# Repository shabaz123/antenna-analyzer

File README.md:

# Antenna Analyzer
This repository contains the detail to construct a VHF/UHF antenna analyzer instrument designed by VK5JST (Amateur Radio, May 2005). Refer to the original article for more information concerning it. The design was entered into KiCad software by TDARS, to create the printed circuit boards described here.

# Overview
The analyzer has two connections; one from the radio transmitter (2W max, but you could use an attenuator), and one to the antenna. Note that the instrument also supports HF, but you'll still need to limit power to 2W max, or use an attenuator.

There's a 4-position rotary selector knob. By using that, it is possible to select SWR or R/Z modes, and observe these values on the built-in moving-coil meter movement. The meter is fitted with a detailed scale, although the diagram here just shown LO/HI.

# Circuit Diagram

# One-Time Calibration
To calibrate the instrument one-time after building it, you just need a HF signal source of adjustable power. Do the following:

(1) Connect a low-power HF source to the RF input on the instrument, and ensure that nothing is attached to the antenna connector (to simulate a bad antenna)

(2) Set the selector knob to the leftmost position which is the **Check Input** position.

(3) Slowly ramp up the input power until the meter scale reaches the center of the '**INPUT OK**' section, which may occur at about 1W of transmitted power

(4) Set the selector knob to next position (**Set FSD**), and then adjust the **front panel potentiometer** until the needle reaches the full scale position

(5) Set the selector knob to the next position (**SWR**), and adjust the trimmer resistor labeled **TP1** to place the needle at the full scale position again

(6) Set the selector knob to the last remaining position (**R/Z**) and adjust the trimmer resistor labeled **TP2** to place the needle again at the full scale position

(7) All is done!

# Using It

In normal use, connect the instrument up to your transmitter (maximum 2W! or use an attenuator) as well as your antenna. Then, follow these steps:

(1) Turn the selector knob to the Set FSD position, and then, at your desired transmit frequency, transmit at approximately half a Watt, or 1W (2W max! or use an attenuator). Turn the rotary potentiometer on the front panel until the meter needle is at max.

(2) Now you are free to select either the SWR or R/Z positions, and examine the values. A good SWR value will be low (leftmost on the meter dial), and a good impedance value will be 50 ohms (close to the center of the meter dial).

(3) By slowly varying the transmit frequency, you should be able to find the antenna resonant frequency, by looking at the impedance. Picture a valley. If you traverse from low to high frequency, then the impedance will reduce down toward 50 ohm, and then beyond a certain frequency it will start increasing. The impedance valley bottom location is where the antenna is resonant.

# Main Circuit Board (with snap-off areas)
The instrument is built using a printed circuit board that has snap-away sections for the rotary controls. Most of the parts are large surface-mount, which is easy to assemble using a good pair of tweezers and a decent soldering iron. Note: Don't solder the BNC and N sockets, until you've looked at the section further below titled 'End Panel'.

This is what the underside looks like:

As you can see, there are snap-off areas for the controls. Note that the PCB manufacturer may ask for an additional charge subsequently as a result of that. For instance, see JLC PCB rules here: https://jlcpcb.com/help/article/in-what-cases-will-there-be-charged-extra

# Alternative Main Circuit Board (with no snap-off areas)
If desired, you could order a PCB without the snap-off areas. You'd need to manually wire the controls (rotary switch and potentiometer) and resistor R8, or use a Flex PCB which is described further below. 

# Wire Link! And Flex Connector Orientation

Important - don't forget to solder the wire link on the main board! It should be soldered on the underside as shown in the photo (so that the PCB ground plane can shield it from the component side).

Also, note how the flex connector is oriented in the photo below. This orientation will hopefully allow it to make good contact with the copper side of the flex PCB.

# Enclosure Planning
You could 3D-print an enclosure if desired. There are two existing 3D printed enclosure styles, developed by Paul M0PLA.

The difference is that style V3 has a sloped top. To print either of them, download the [style V1 STL file](https://github.com/shabaz123/antenna-analyzer/raw/refs/heads/main/3d-renders/swr-box-v1.stl) or the [style V3 STL file](https://github.com/shabaz123/antenna-analyzer/raw/refs/heads/main/3d-renders/swr-box-v3.stl) and 3D-print it (or use a 3D print service).

A wood enclosure is another possibility.
For the full set of dimensions, refer to the "Dimensions" section further below.

Use the front panel PCB, and the end panel PCB, as guides to create the enclosure, and confirm they will fit.

# Flex PCB Controls
If you like, you could use a flexible PCB for the controls and resistor R8. This is what the design looks like:

Here is the 3D view of it:

Here is the underside view of it:

The potentiometer and rotary switch bodies both have a little protrusion key that is used to prevent them rotating along with the shaft. The top panel PCB does not have keyholes for that, so you'll need to dremel or file off the protrusions or find some other way of removing them. I used heavy-duty wire cutters, but it will probably damage the cutters slightly. 
You could use epoxy glue to secure the potentiometer bodies as shown in the photos below. I decided not to use the shaft nuts to secure the potentiometer and rotary switch, because I wanted to recess them a little bit, and I just used glue. Perhaps a 3D-printed mount could be glued onto the underside of the top panel, to make them flush from the top side.

Here is what it looks like when the flex PCB is assembled:

To use this flex PCB, you'll need to attach a Flat Flexible Cable (FFC) connector onto the mainboard:

The connector is available from AliExpess, search for **FPC 2.54mm Pitch Connector Flat Flexible Cable** and select an 8-way connector. There are straight and right-angle options. The 3D render above shows a right-angle connector, but a straight connector is probably easier to install without hitting the meter. 

## Important: Connector Orientation
Install the connector such that the Pin 1 marking on the flexible PCB mates with Pin 1 on the mainboard, which is indicated by a square pad. 

NOTE: You also have to ensure that the springy side of the terminal inside the connector mates with the copper side of the flexible PCB, to make good contact. If you're unsure, use a multimeter set to continuity mode and check there is good contact before soldering the connector. This will help eliminate the risk of installing the connector the wrong way around.

# End Panel
If you don't have the ability to drill holes, then optionally, an end panel printed circuit board can be created too. This eliminates needing to drill any holes.

The BNC and N sockets are simply screwed onto the panel (order is: put crinkle washer on first, then the ring tag, then the nut), and the ring tags can be soldered down (it will be easier if you slightly bend the ring tag terminal beforehand).

After you've done that, the BNC and N connectors can be soldered to the main board PCB and then solder the edge of the main board against the horizontal bare copper area on the end panel. 

NOTE: It's probably a good idea to use epoxy glue to secure the RF connectors to their nuts, and to the PCB, so that the RF connectors cannot rotate even slightly (which would tear the RF connector center pin connection to the PCB tracks!

# Meter Dial
To remove the existing meter dial (100uA scale) remove the meter side ears (they look like paddles, they might not be fitted to the meter as supplied). Next, carefully remove the black bezel from the meter. It just unclips, if you gently bend the side lobes of the bezel just a fraction of a degree (careful, they can break!).

There is a white wedge-shaped meter zero position adjustment on the front of the meter. Rotate it so that the white wedge is centered for now. Next, unscrew the two small screws that hold the front clear plastic to the meter, and carefully lift off the front plastic. This is easier when that white wedge has been centered. 

You'll see that the meter dial/scale is a thin aluminium plate that has been painted white with black lettering. Unscrew the two screws that hold the meter dial to the meter, and then slide it out, without accidentally bending the meter needle!

There are two options as to how to replace the meter dial.

(1) Print off the [SVG meter dial](https://github.com/shabaz123/antenna-analyzer/raw/refs/heads/main/images/meter-dial-antenna-analyzer.svg) onto a sheet of paper (you may have to experiment with it to size it perfectly) and then cut and glue it to the plain aluminium side of the existing meter dial. An excellent thin watery glue is "Tombow Mono Multi Liquid Glue" intended for cardboard.

(2) Use the [meter dial Gerber file](https://github.com/shabaz123/antenna-analyzer/raw/refs/heads/main/gerbers/meter-dial-antenna-analyzer-gerbers.zip) and upload it to a PCB manufacturer website, selecting 0.8 mm thickness aluminium PCB. When it arrives, it should be a direct replacement for the existing meter dial, although it will be slightly thicker (ideally it would be 0.25 - 0.3 mm thick, but that's not feasible at a reasonable cost from PCB manufacturers).

# Top Panel
Optionally, if desired, you could use the top panel printed circuit board, if you don't have a way to cut out a meter panel rectangular hole. The top panel eliminates needing to cut out anything!

The meter side ears are removed, then carefully unclip the black bezel and then insert the bezel into the top panel, and then the meter is fitted to the bezel from below the top panel, and then the side ears are fitted on, and rotated until the meter is held in position firmly.

# Final Assembly

The top panel is screwed into the enclosure first. Then, the end panel (with the main board soldered on) is brought into position, to plug in the flex PCB. 

The photo here shows the flex PCB plugged into the main board:

Screw the end panel into position.

All is complete, ready for testing and calibration!

# Dimensions
The information in these photos/diagrams may be helpful if you're designing an enclosure.

# Ordering the Circuit Boards

You'll need the following zip files:

[main-board-gerbers.zip](https://github.com/shabaz123/antenna-analyzer/raw/refs/heads/main/gerbers/main-board-gerbers.zip)

[end-panel-gerbers.zip](https://github.com/shabaz123/antenna-analyzer/raw/refs/heads/main/gerbers/end-panel-gerbers.zip)

[top-panel-gerbers.zip](https://github.com/shabaz123/antenna-analyzer/raw/refs/heads/main/gerbers/top-panel-gerbers.zip)

[meter-dial-antenna-analyzer-gerbers.zip](https://github.com/shabaz123/antenna-analyzer/raw/refs/heads/main/gerbers/meter-dial-antenna-analyzer-gerbers.zip)

If you intend to go the flexible controls PCB route, then you don't need the main-board-gerbers.zip file, and instead, you need to replace that with these two files:

[mainboard-only-no-snap-off-areas.zip](https://github.com/shabaz123/antenna-analyzer/raw/refs/heads/main/gerbers/mainboard-only-no-snap-off-areas.zip)

[controls-flex-gerbers.zip](https://github.com/shabaz123/antenna-analyzer/raw/refs/heads/main/gerbers/controls-flex-gerbers.zip)

To order, go to any PCB manufacturer, e.g. JLCPCB, register for an account, then click on **Order Now** and then click on **Add Gerber File**. 

Select one of the zip files and upload it. You can accept all the defaults, but feel free to play around with the PCB color options (some may cost more, or take a couple of days longer to manufacture). Optionally, select **Remove Mark** which is in the **Mark on PCB** section (if you don't select Remove Mark, then a little serial number will appear on your board, and you might not want that for cosmetic reasons). Once you're done, click the **Save to Cart** button. 

Repeat for the other zip files as required. For the meter dial, make sure you select 0.8 mm thickness, rather than the default 1.6 mm thickness. When you checkout the order, you'll see a list of all of the boards that you uploaded. Click on the checkbox on the left side, to select all the items. 

Note: If you're ordering the flexible controls PCB, then you need to perform the following steps:

Select **Global Shipping Direct Line**, which is usually the far cheaper delivery option. You can confirm the price in the box on the right, prior to finally paying (with, say PayPal).

Note that if you're ordering the flexible PCB, then it's highly recommended to select the 'Payment after Review' option, so that the manufacturer can e-mail you any queries that they may have. If they have trouble understanding what the flexible PCB is supposed to look like, you could send them the flex PCB layout and 3D render screenshots, so that they have some context.

# Parts List

The PDF parts list is downloadable here: 

[parts-list.pdf](https://github.com/shabaz123/antenna-analyzer/raw/refs/heads/main/components/parts-list.pdf)

**NOTE**: The PDF parts list is missing the Flat Flex Cable (FFC) connector, which is optional, it is only required if you're using the flex PCB.

The contents are reproduced here for convenience (including the FFC connector):

**Row**|**Identifier**|**Value**|**Qty**|**Description**|**Source**|**Part Code**|**Approx Total GBP**
:-----:|:-----:|:-----:|:-----:|:-----:|:-----:|:-----:|:-----:
1|R1,R2,R3|3 x 150R Parallel|9|1206 150 ohm Resistor Thick Film 0.75W|Mouser|SG73P2BTTD151G|0.55
2|R4|15k|1|0805 Resistor|Mouser|RCG080515K0FKEA|0.12
3|R5|10k|1|0805 Resistor|Mouser|RCG080510K0FKEA|0.12
4|R6|27k|1|0805 Resistor|Mouser|RCS080527K0FKEA|0.27
5|R7|56k|1|0805 Resistor|Mouser|RCS080556K0FKEA|0.11
6|R8|470R|1|0805 Resistor|Mouser|CRCW0805470RFKEA|0.07
7|C1,C2,C3|470p|3|0805 Capacitor NP0 470pF|Mouser|08055A471J4T2A|0.54
8|C4,C5,C6|100n|3|0805 Capacitor X7R 100nF|Mouser|KAM21BR71H104JT|0.21
9|D1,D2,D3|1N5711W-7-F|3|Schottky Diode SOD-123|Mouser|1N5711W-7-F|0.35
10|TP1,TP2|10k Trimmer|2|Trimmer Resistor 10k 3386P|Mouser|3386P-1-103T|3.68
11|SK3|BNC Socket|1|BNC Socket 031-221-RFX|Mouser|031-221-RFX|2.49
12|SK4|N Socket|1|N Socket 1-1337417-0|Mouser|1-1337417-0|6.18
13|M1|100uA Panel Meter|1|85C17 100uA Panel Meter|AliExpress|85C17 100uA|3.41
14|P1|5k LIN (B) Potentiometer|1|RV097 Linear (B) 5k Potentiometer |AliExpress|RV097 B 5k|0.41
15|SW1|RS1010 Rotary Switch|1|RS1010 2 Pole 4 Way Switch|AliExpress|RS1010 2 Pole 4|0.88
16|n/a|Knob|2|Potentiometer Knob 10mm dia|AliExpress|Knob Flower Axis Diameter 10mm|0.38
17|n/a|8-way Cable|1|2.54 mm Pitch Grey Flat Cable 70mm|AliExpress|2.54mm Flat Cable 8P 70mm|0.29
18|n/a|4-way Cable|1|2.54 mm Pitch Grey Flat Cable 70mm|AliExpress|2.54mm Flat Cable 4P 70mm|0.28
19|n/a|FFC Connector|1|FPC 2.54mm Pitch Connector Flat Flexible Cable 8-way Straight (ideally)|AliExpress|FPC 2.54mm Pitch Connector Flat Flexible Cable Straight|0.17

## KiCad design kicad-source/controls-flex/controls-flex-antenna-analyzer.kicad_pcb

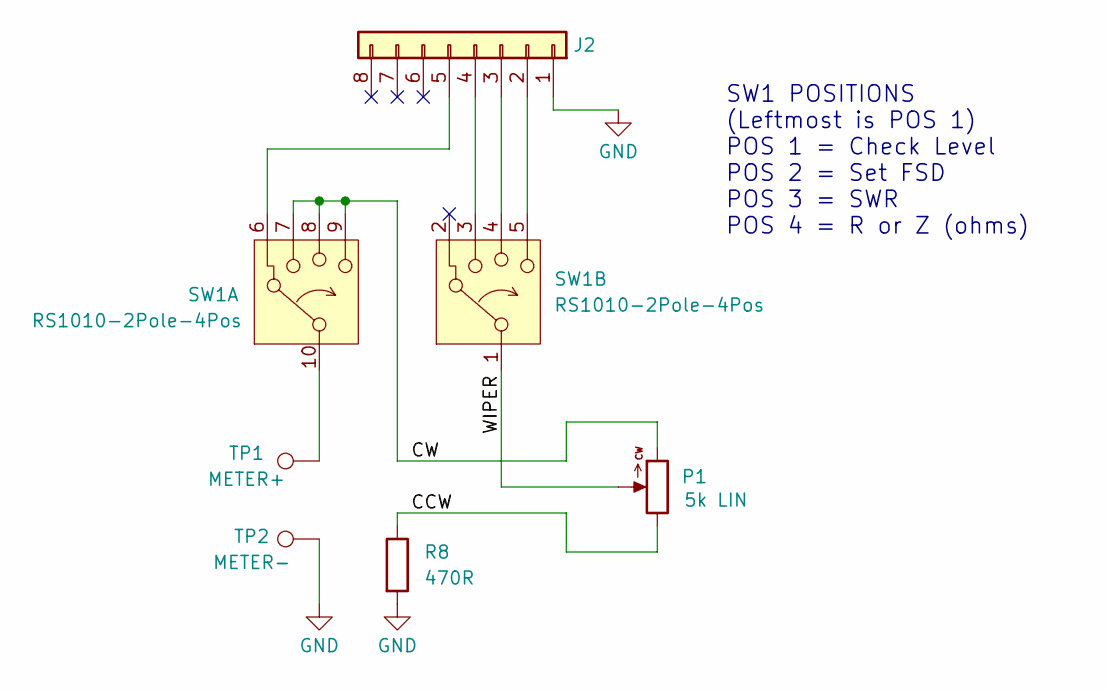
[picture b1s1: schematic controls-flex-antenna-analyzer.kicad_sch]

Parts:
J2: flex-8way-2.54
P1: 5k LIN; Potentiometer_RD701F
R8: 470R; R_0805_2012Metric_Pad1.20x1.40mm_HandSolder
SW1: RS1010-2Pole-4Pos; RS1010
TP1: METER+; TestPoint_Plated_Hole_1.8mm
TP2: METER-; TestPoint_Plated_Hole_1.8mm

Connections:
/CCW: P1.1, R8.1
/CW: P1.3, SW1.7, SW1.8, SW1.9
/WIPER: P1.2, SW1.1
GND: J2.1, R8.2, TP2.1
unnamed: J2.2, SW1.5
unnamed: J2.3, SW1.4
unnamed: J2.4, SW1.3
unnamed: J2.5, SW1.6
unnamed: SW1.10, TP1.1

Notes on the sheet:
SW1 POSITIONS (Leftmost is POS 1) POS 1 = Check Level POS 2 = Set FSD POS 3 = SWR POS 4 = R or Z (ohms)

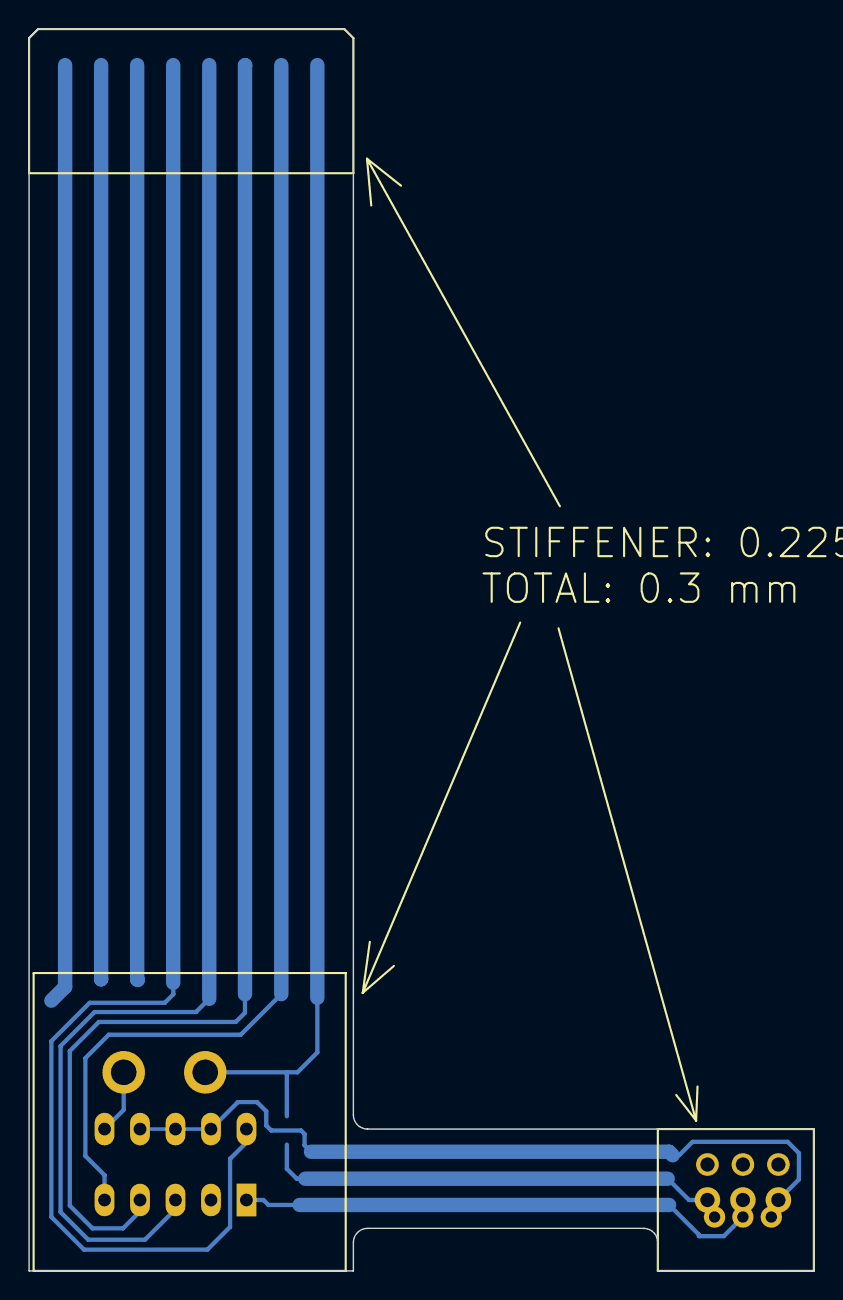
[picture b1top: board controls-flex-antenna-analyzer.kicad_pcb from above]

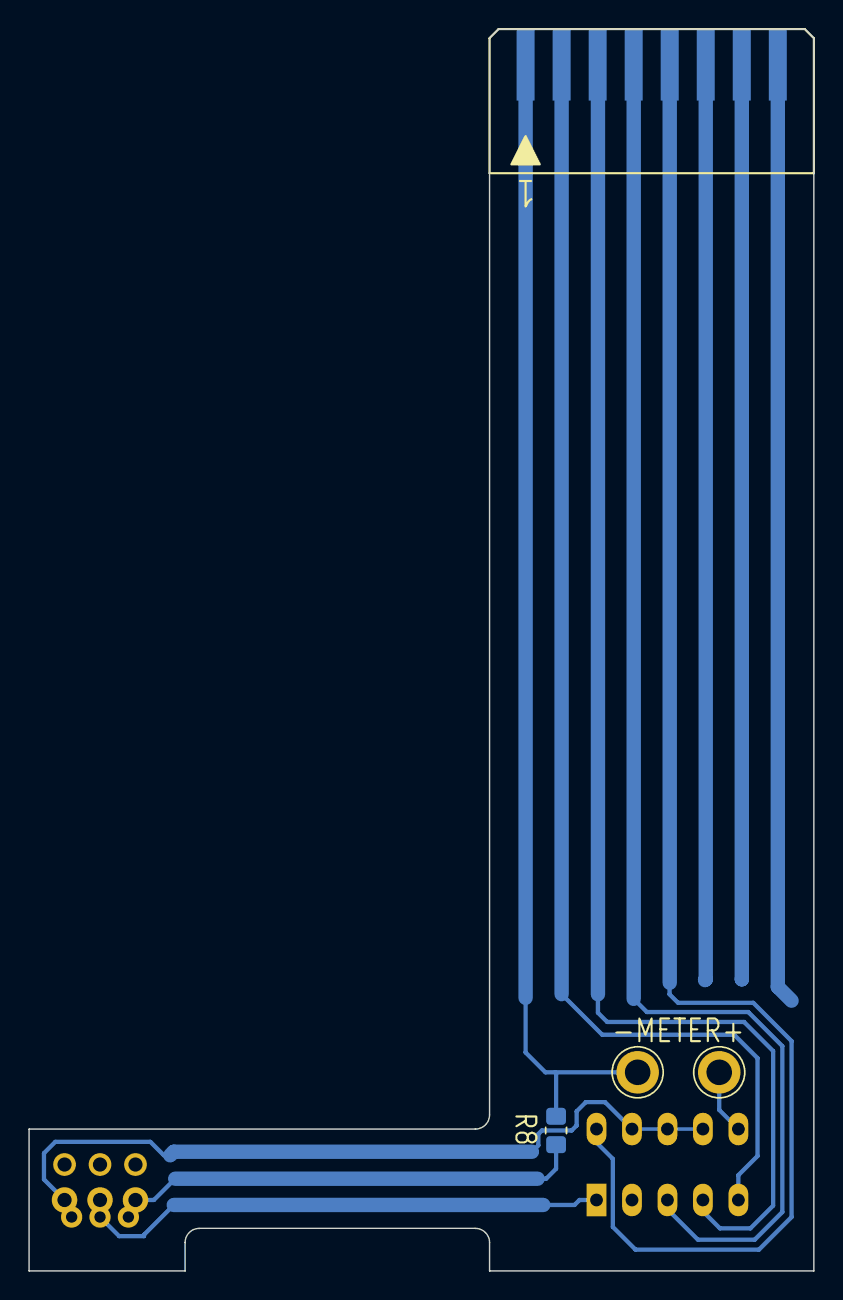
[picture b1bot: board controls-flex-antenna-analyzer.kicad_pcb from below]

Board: 2 copper layers, 55.3 x 87.5 mm, 6 parts (4 on the bottom side), 9 nets.

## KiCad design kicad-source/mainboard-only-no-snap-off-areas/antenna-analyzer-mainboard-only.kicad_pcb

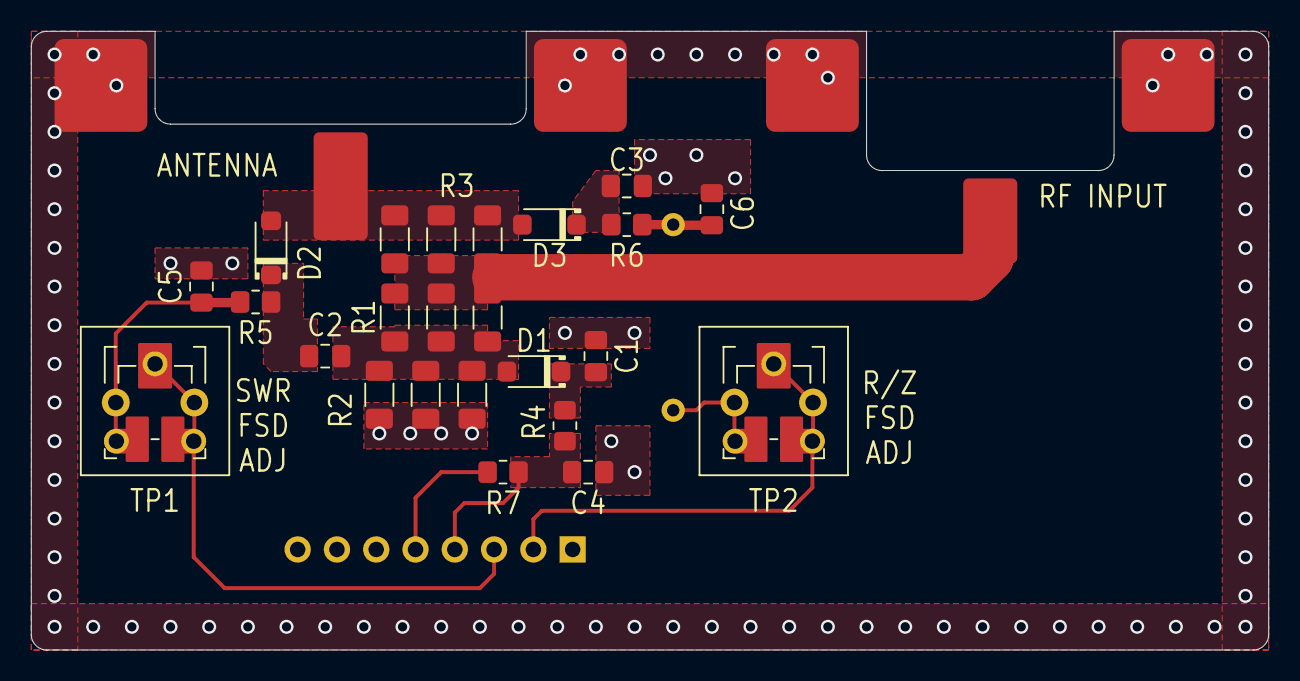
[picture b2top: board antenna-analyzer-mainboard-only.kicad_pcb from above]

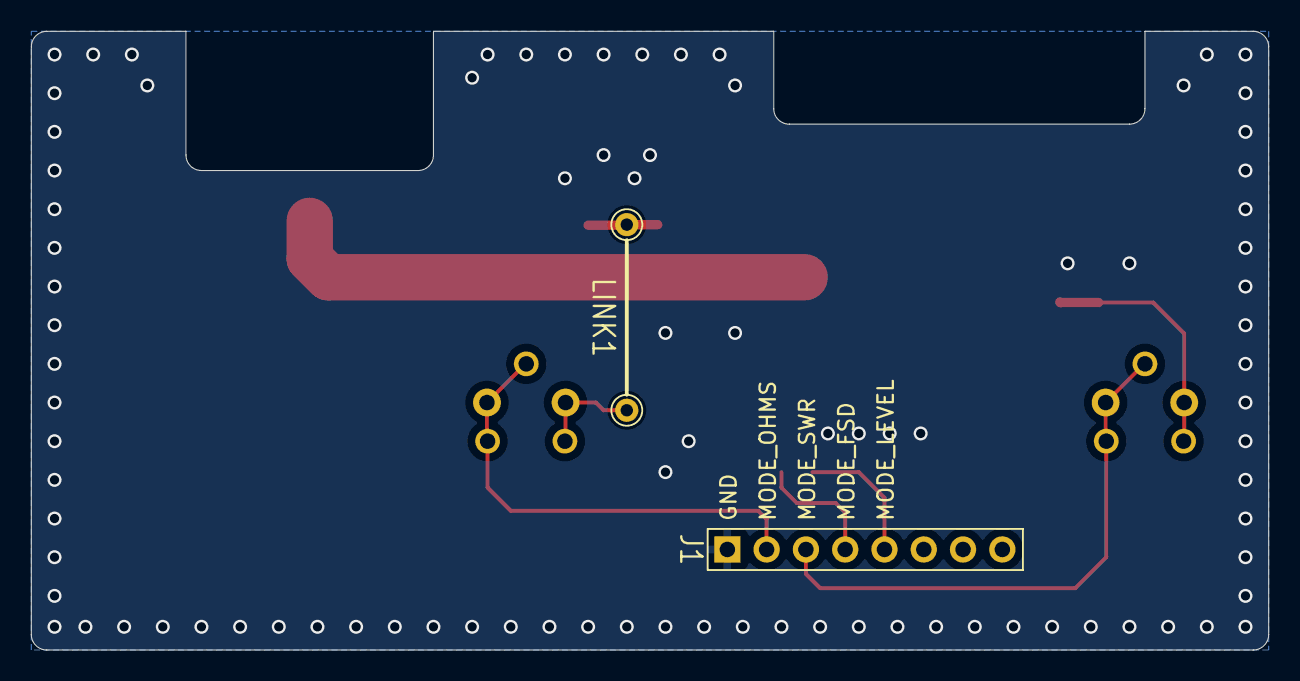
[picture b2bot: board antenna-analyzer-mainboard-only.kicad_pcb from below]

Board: 2 copper layers, 80.0 x 40.0 mm, 22 parts (2 on the bottom side), 14 nets.

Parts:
C1, C2, C3: 470p; C_0805_2012Metric_Pad1.18x1.45mm_HandSolder
C4, C5, C6: 100n; C_0805_2012Metric_Pad1.18x1.45mm_HandSolder
D1, D2, D3: 1N5711; D_SOD-123
J1: PinHeader_1x08_P2.54mm_Vertical
LINK1: wire-link-shorted; wire-link-12mm
R1, R2, R3: 3 x 150R Parallel; 1206-triple-parallel
R4: 15k; R_0805_2012Metric_Pad1.20x1.40mm_HandSolder
R5: 10k; R_0805_2012Metric_Pad1.20x1.40mm_HandSolder
R6: 27k; R_0805_2012Metric_Pad1.20x1.40mm_HandSolder
R7: 56k; R_0805_2012Metric_Pad1.20x1.40mm_HandSolder
SK3: RF INPUT 2W MAX BNC Socket; BNC Socket Edge 031-221-RFX
SK4: ANTENNA N Socket; N Socket Edge 1-1337417-0
TP1, TP2: 10k; Potentiometer_Trimmer_Generic_Vertical

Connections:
/MODE_FSD: C4.2, J1.4, R4.2, R7.1
/MODE_LEVEL: J1.5, R7.2
/MODE_OHMS: J1.2, TP2.1, TP2.2
/MODE_SWR: J1.3, TP1.1, TP1.2
/RECT_VA: C1.2, D1.3 (K), R4.1
/RECT_VB: C3.1, D3.3 (K), R6.1
/RECT_VDIFF: C2.2, D2.3 (K), R5.1
/RF_IN: R1.1, R3.1, SK3.1 (In)
/VA: C2.1, D1.1 (A), R1.2, R2.1
/VB: D2.1 (A), D3.1 (A), R3.2, SK4.1 (In)
GND: C1.1, C3.2, C4.1, C5.2, C6.2, J1.1, R2.2, SK3.2 (Ext), SK4.2 (Ext)
unnamed: C5.1, R5.2, TP1.3
unnamed: C6.1, LINK1.2 (A), R6.2
unnamed: LINK1.1 (K), TP2.3
